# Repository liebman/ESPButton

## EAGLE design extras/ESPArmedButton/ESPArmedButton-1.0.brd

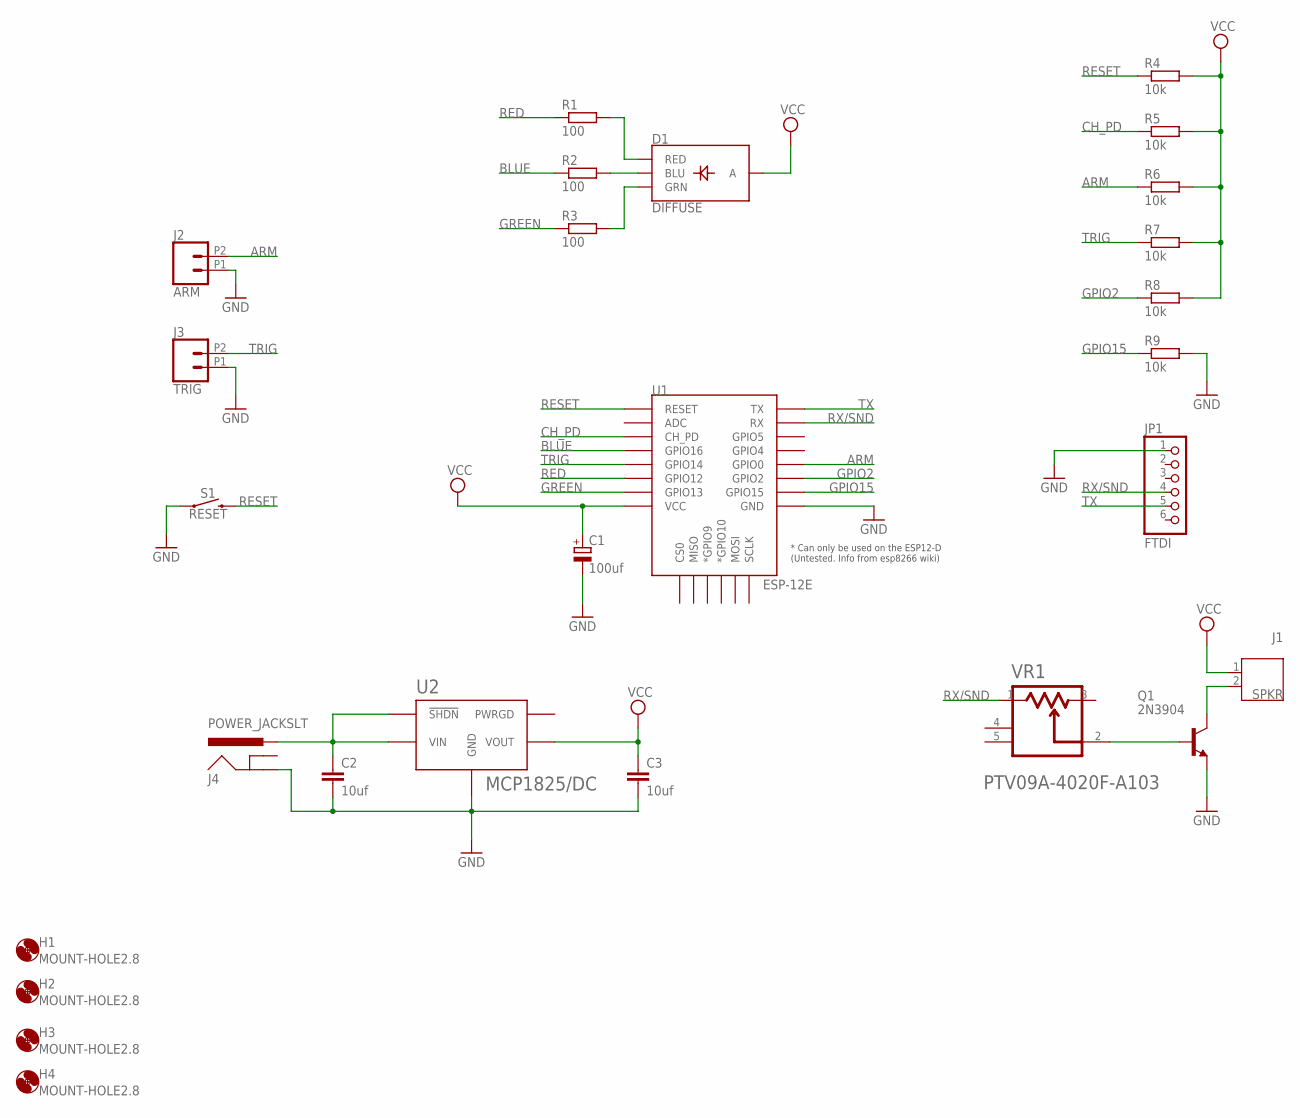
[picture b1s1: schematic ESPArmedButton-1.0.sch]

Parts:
C1: 100uf; E2-5
C2, C3: 10uf; C050-025X075
D1: DIFFUSE; LED-RGB-THRU
H1, H2, H3, H4: MOUNT-HOLE2.8; 2,8
J1: SPKR; JST-PH2
J2: ARM; 1X02_2.54_SCREWTERM
J3: TRIG; 1X02_2.54_SCREWTERM
J4: POWER_JACKSLT; POWER_JACK_SLOT
JP1: FTDI; 1X06/90
Q1: 2N3904; TO92
R1, R2, R3: 100; 0207/7
R4, R5, R6, R7, R8, R9: 10k; 0207/7
S1: RESET; TACTILE_SWITCH_PTH_6.0MM
U1: ESP-12E; ESP12E-SMD
U2: MCP1825/DC; SOT-223-5
VR1: BOURNS_PTV09A-4020F-A103BOURNS_PTV09A-4020F-A103_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; BOURNS_PTV09A-4020F-A103_0

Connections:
ARM: J2.P2 (2), R6.1, U1.GPIO0
BLUE: R2.1, U1.GPIO16
CH_PD: R5.1, U1.CH_PD
GND: C1.-, C2.2, C3.2, J2.P1 (1), J3.P1 (1), J4.GND@1 (GND), JP1.1, Q1.3 (E), R9.2, S1.1, U1.GND, U2.P$3 (GND), U2.P$6 (GND)
GPIO2: R8.1, U1.GPIO2
GPIO15: R9.1, U1.GPIO15
GREEN: R3.1, U1.GPIO13
unnamed: Q1.2 (B), VR1.2
unnamed: J1.2, Q1.1 (C)
unnamed: D1.4 (BLU), R2.2
unnamed: D1.1 (RED), R1.2
unnamed: D1.3 (GRN), R3.2
RED: R1.1, U1.GPIO12
RESET: R4.1, S1.3 (2), U1.RESET
RX/SND: JP1.4, U1.RXD0 (RX), VR1.1
TRIG: J3.P2 (2), R7.1, U1.GPIO14
TX: JP1.5, U1.TXD0 (TX)
VCC: C1.+, C3.1, D1.2 (A), J1.1, R4.2, R5.2, R6.2, R7.2, R8.2, U1.VCC, U2.P$4 (VOUT)
VIN: C2.1, J4.PWR, U2.P$1 (!SHDN), U2.P$2 (VIN)

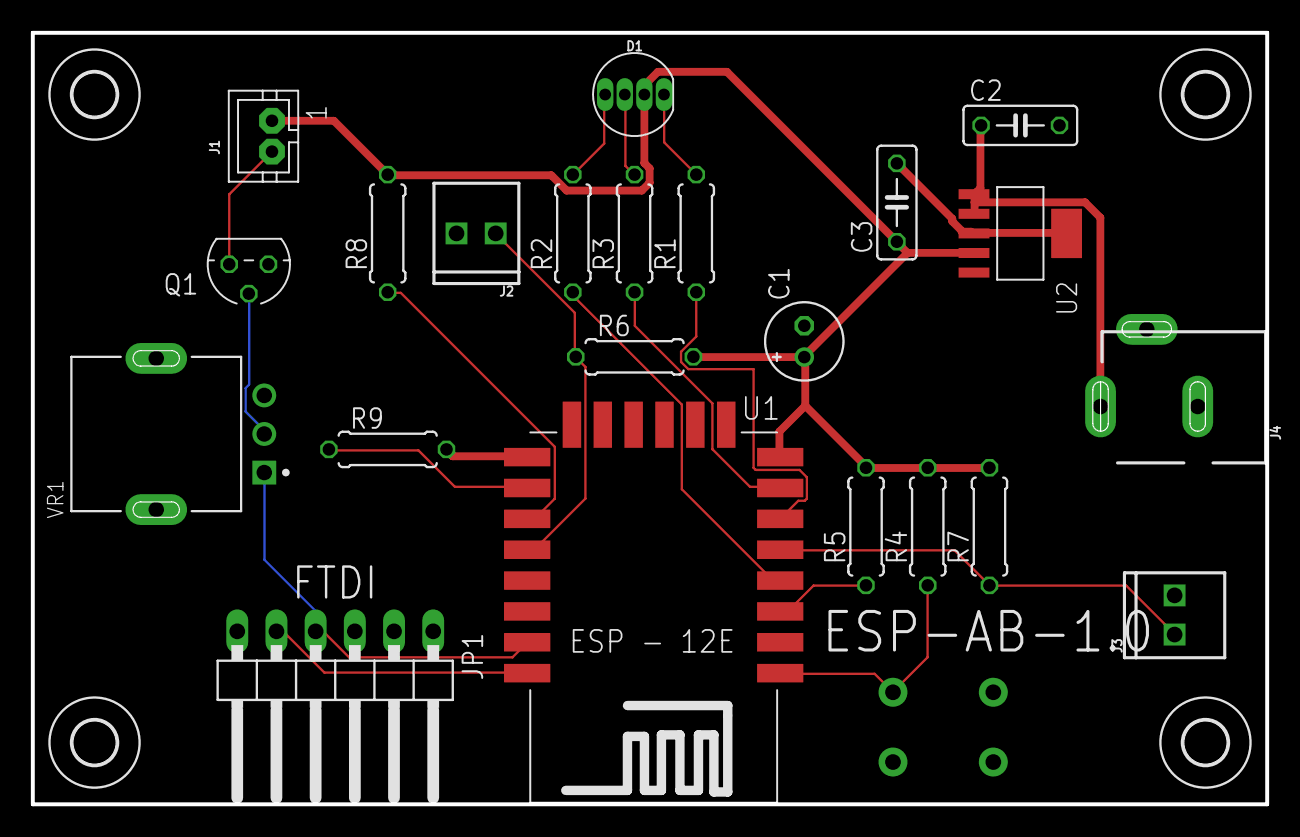
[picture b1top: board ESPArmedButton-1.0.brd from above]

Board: 2 copper layers, 80.0 x 50.0 mm, 27 parts (1 on the bottom side), 19 nets.

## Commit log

2018-03-18 initial version
2018-07-06 basic reorg / added submodules for libraries and core
2018-07-07 patch WiFiManager for WPS change in core
2018-07-07 updated to support bear ssl http client
2018-07-08 started using bearssl
2018-07-15 working checkpoint
2018-07-16 update WiFiManager
2018-08-06 updates/fixes - still debugging
2018-09-22 updated WiFiManager & esp8266 core
2018-12-09 WIP - update core
2018-12-09 deleted submodule ESP8266_Spiram
2018-12-09 updated ArduinoJson and ESP8266Audio
2018-12-16 update core & libs
2018-12-16 add some speach, its a rough first cut
2018-12-16 Functional voicing
2019-01-21 hacked - still have memory issue on esp8266 :-(
2019-01-21 add esp32 arduino core
2019-02-21 Saved version just in case - will remove later
2019-02-21 new version
2019-02-21 working version of core
2019-02-21 working but still WIP
2019-02-21 working with latest esp8266 core
2019-02-22 updated core / fix name in spiffs script
2019-02-23 Working basic configuration
2019-02-23 update to current git core
2019-02-24 Added update via http
2019-02-24 testing with syslog
2019-02-24 working without audio
2019-02-24 uworking with audio but not enough mem for ssl :-(
2019-02-25 use patched ESP8266SAM use green led for http update
2019-03-02 adjusted say phrases
2019-03-02 update SAM with more memory savings adjust phrases
2019-03-02 add syslog and phrases to config
2019-03-03 save/load syslog in config
2019-03-03 Don't enter configure if the reset reason was soft reset
2019-03-03 update needs to be after wifi init
2019-03-09 updates for SAM & core + use default ntp server if WN returns empty string
2019-03-16 esp8266 core update
2019-03-30 save SSID and PSK in config file save config before WiFiManager attempts connect
2019-03-30 add EAGLE files
2019-03-30 Create LICENSE
2019-03-30 first attempt at travis build
2019-03-30 added mostly empty README
2019-03-30 reformat .travis.yml
2019-03-30 added build icon

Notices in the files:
parts and their libraries:
SparkFun-Connectors: Licensing: Creative Commons ShareAlike 4.0 International - https://creativecommons.org/licenses/by-sa/4.0
